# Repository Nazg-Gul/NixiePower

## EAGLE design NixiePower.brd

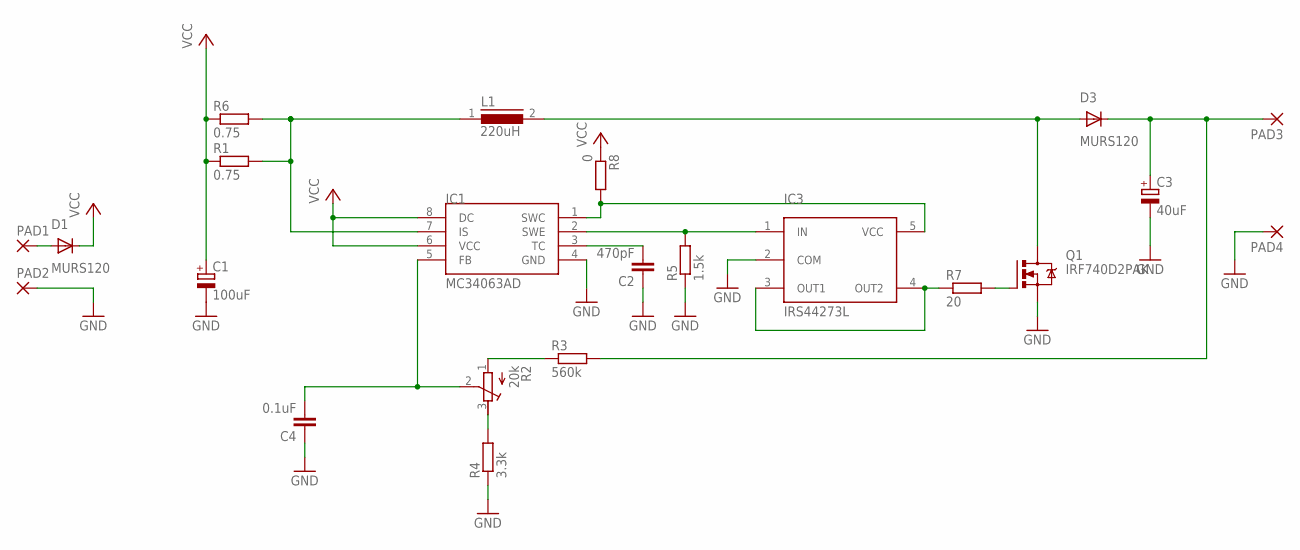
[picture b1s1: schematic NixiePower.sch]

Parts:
C1: 100uF; D/7343-31R
C2: 470pF; C1206K
C3: 40uF; C/6032-28R
C4: 0.1uF; C1206K
D1, D3: MURS120; DO214AA
IC1: MC34063AD; SOIC8
IC3: IRS44273L; SOT23-5
L1: 220uH; DR125
PAD1, PAD2, PAD3, PAD4: SMD5; SMD2,54-5,08
Q1: IRF740D2PAK; D2PAK
R1, R6: 0.75; R1206
R2: 20k; RTRIM4G/J
R3: 560k; R1206
R4: 3.3k; R1206
R5: 1.5k; R1206
R7: 20; R1206
R8: 0; R1206

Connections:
GND: C1.-, C2.1, C3.-, C4.1, IC1.4 (GND), IC3.2 (COM), PAD2.1, PAD4.1, Q1.3 (S), R4.1, R5.1
unnamed: D3.A, L1.2, Q1.4 (D)
unnamed: C2.2, IC1.3 (TC)
unnamed: IC1.7 (IS), L1.1, R1.2, R6.2
unnamed: IC1.1 (SWC), IC3.5 (VCC), R8.2
unnamed: Q1.1 (G), R7.2
unnamed: C3.+, D3.C, PAD3.1, R3.2
unnamed: C4.2, IC1.5 (FB), R2.2 (S)
unnamed: IC3.3 (OUT1), IC3.4 (OUT2), R7.1
unnamed: R2.1 (A), R3.1
unnamed: R2.3 (E), R4.2
unnamed: IC1.2 (SWE), IC3.1 (IN), R5.2
unnamed: D1.A, PAD1.1
VCC: C1.+, D1.C, IC1.6 (VCC), IC1.8 (DC), R1.1, R6.1, R8.1

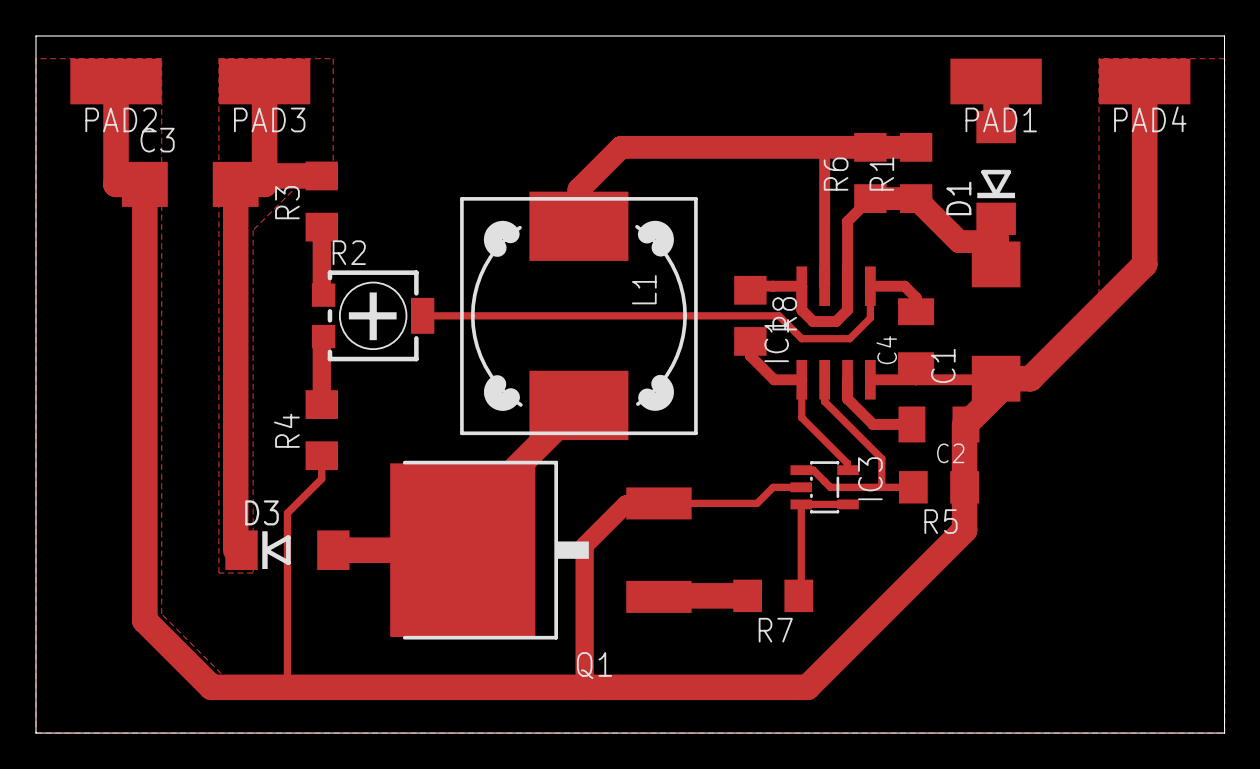
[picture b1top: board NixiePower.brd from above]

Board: 2 copper layers, 66.0 x 38.7 mm, 22 parts (0 on the bottom side), 14 nets.

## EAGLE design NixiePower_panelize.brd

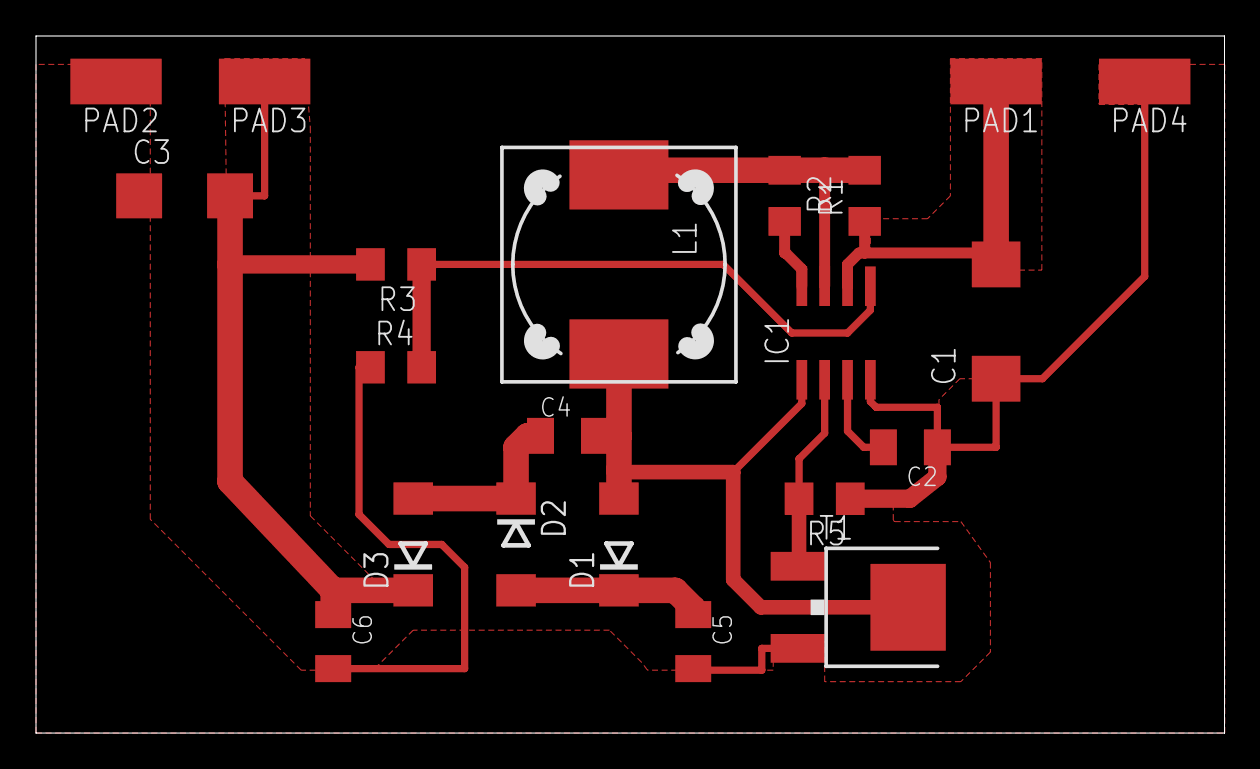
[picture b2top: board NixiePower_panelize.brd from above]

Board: 2 copper layers, 66.0 x 38.7 mm, 21 parts (0 on the bottom side), 11 nets.

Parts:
C1: 100uF; D/7343-31R
C2: 400pF; C1206K
C3: 40uF; C/6032-28R
C4, C5, C6: 470nF; C1206K
D1, D2, D3: MURS120; DO214AA
IC1: MC34063AD; SOIC8
L1: DR125
PAD1, PAD2, PAD3, PAD4: SMD2,54-5,08
R1: 0.5; R1206
R2: 180; R1206
R3: 47k; R1206
R4: 2.2k; R1206
R5: R1206
T1: MJD31; DPAK

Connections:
GND: C1.-, C2.1, C3.-, C5.2, C6.2, IC1.4, PAD2.1, PAD4.1, R4.1, R5.1, T1.3
unnamed: C4.2, D1.A, IC1.1, L1.2, T1.4
unnamed: C2.2, IC1.3
unnamed: IC1.7, L1.1, R1.2, R2.1
unnamed: IC1.8, R2.2
unnamed: C1.+, IC1.6, PAD1.1, R1.1
unnamed: IC1.5, R3.1, R4.2
unnamed: C5.1, D1.C, D2.A
unnamed: C4.1, D2.C, D3.A
unnamed: C3.+, C6.1, D3.C, PAD3.1, R3.2
unnamed: IC1.2, R5.2, T1.1

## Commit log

2017-01-21 Initial commit of Rev.A
2017-01-21 Commit of Rev.B version
2017-01-21 Commit of Rev.C version
2017-01-21 Commit of the current version
